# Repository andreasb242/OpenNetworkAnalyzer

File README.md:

# OpenNetworkAnalyzer
Improved software for https://hackaday.io/project/10021-arduino-network-analyzer

## Hardware
There are different hardware implementations, some based on Arduino, for an easy Start.

### Arduino
*firmware/arduino/ONA_PWM* is a firmware, which does not need any additional hardware.
The Pin *D5* is used as output, without any filtering, the Pin *A0* is used as input.
This firmware can be used to easy check how it's working, wihtout bying / building hardware.

But the output is a rectangular signal, which isn't really working for testing, as a rectangular signal contains different frequenecies instead of one.
Therefore this is only for testing purpose.

*Maximum Frequency* is 62500Hz, really low.

*firmware/arduino/ONA_AD9851* is the Version based on the first software-hackday.io Version.
There is the Arduino Uno Shield, layout located at *layout/hackaday.io-V2.0*.

And there is an Arduino Nano Version, located at *layout/arduino-nano-AD9851*
This board is not tested.

*firmware/arduino/ONA_SI5351*
This implementation is fully working from 4kHz to 175MHz, recommend range is about 1MHz to 100MHz, out of this range there are some issues: at 4kHz the Sinus looks more than a Square wave.
At > 100MHz the signal gets lower.

### STM32 USB
Not yet ready.

## Screenshots

## Installation / running
### Ubuntu
    git clone https://github.com/andreasb242/OpenNetworkAnalyzer.git
    sudo apt install python3-tk python3-numpy python3-serial python3-pil.imagetk
    cd software
    python3 main.py

### Mac OS
    TODO

### Windows
    TODO

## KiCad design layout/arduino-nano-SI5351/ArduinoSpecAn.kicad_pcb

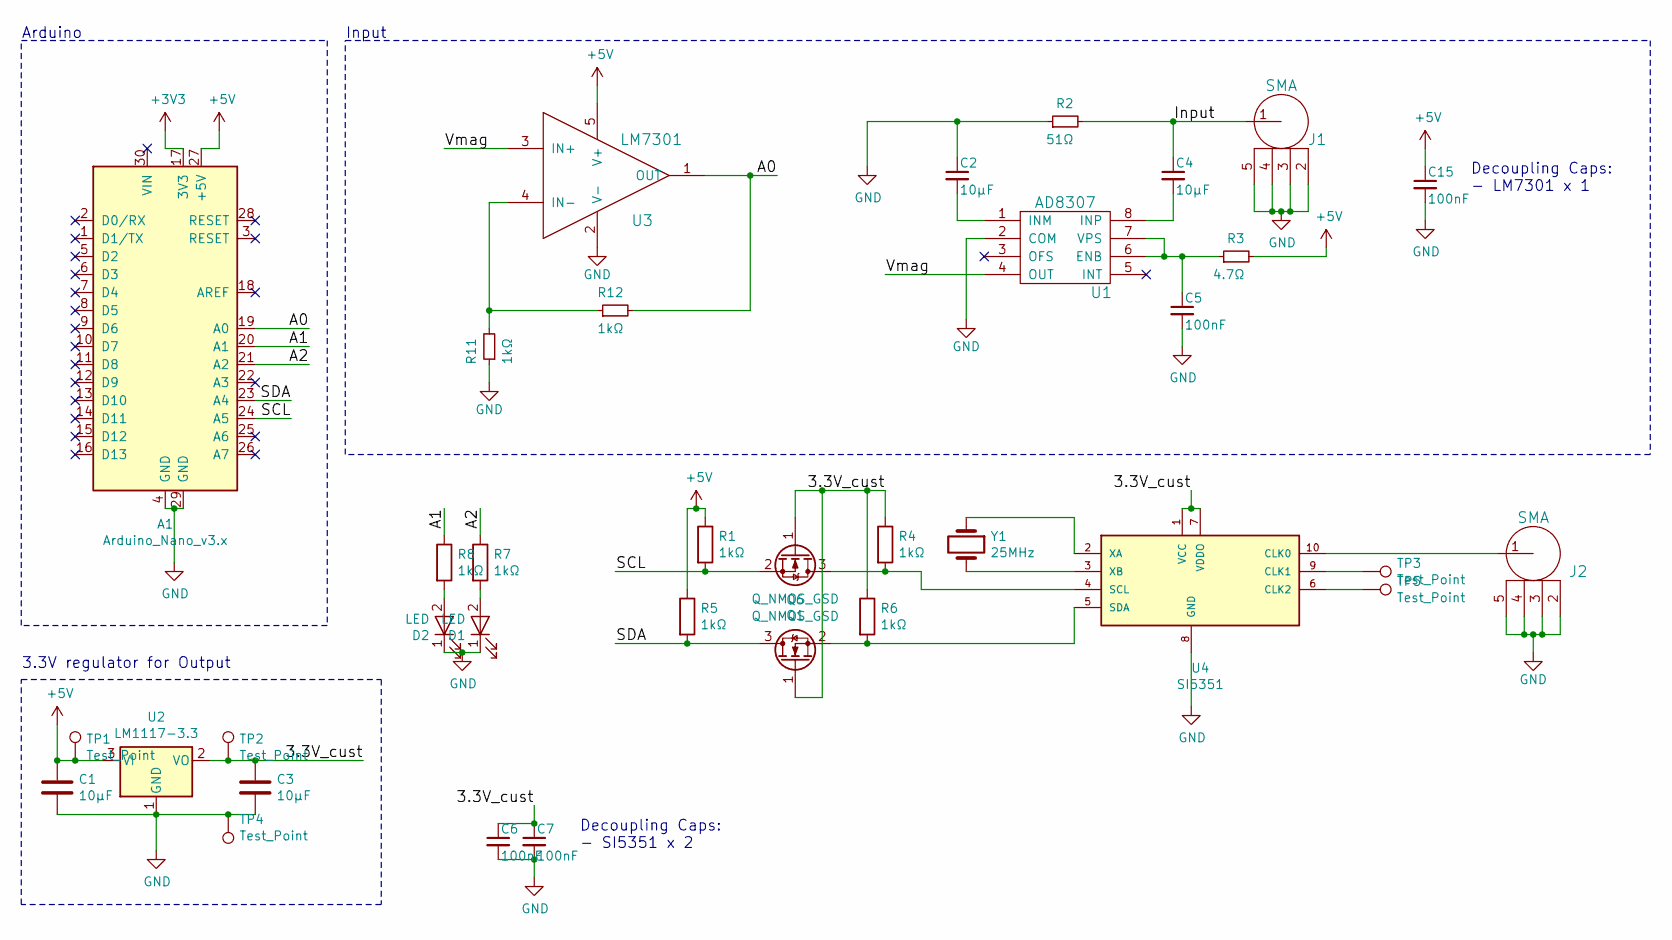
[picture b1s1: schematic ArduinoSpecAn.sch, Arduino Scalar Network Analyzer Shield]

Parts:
A1: Arduino_Nano_v3.x; Arduino_Nano
C1, C2, C3, C4: 10µF; C_0805_2012Metric_Pad1.15x1.50mm_HandSolder
C5, C6, C7, C15: 100nF; C_0805_2012Metric_Pad1.15x1.50mm_HandSolder
D1, D2: LED; LED_0805_2012Metric_Pad0.97x1.50mm_HandSolder
J1, J2: SMA; SMA_Edgemount
Q1, Q6: Q_NMOS_GSD; SOT-23
R1, R4, R5, R6, R7, R8, R11, R12: 1kΩ; R_0805_2012Metric_Pad1.15x1.50mm_HandSolder
R2: 51Ω; R_0805_2012Metric_Pad1.15x1.50mm_HandSolder
R3: 4.7Ω; R_0805_2012Metric_Pad1.15x1.50mm_HandSolder
TP1, TP2, TP3, TP4, TP5: Test_Point; TestPoint_Pad_D1.5mm
U1: AD8307; SOIC-8-N
U2: LM1117-3.3; SOT-223-3_TabPin2
U3: LM7301; SOT-23-5
U4: SI5351; MSOP-10_3x3mm_P0.5mm
Y1: 25MHz; Crystal_HC49-U_Vertical

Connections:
+5V: A1.27 (+5V), C1.1, C15.1, R1.1, R3.2, R5.1, TP1.1, U2.3 (VI), U3.5 (V+)
/3.3V_cust: C3.1, C6.1, C7.1, Q1.1 (G), Q6.1 (G), R4.1, R6.1, TP2.1, U2.2 (VO), U4.1 (VCC), U4.7 (VDDO)
/A0: A1.19 (A0), R12.2, U3.1 (OUT)
/A1: A1.20 (A1), R8.1
/A2: A1.21 (A2), R7.1
/Input: C4.1, J1.1, R2.2
/SCL: A1.24 (A5), Q1.2 (S), R1.2
/SDA: A1.23 (A4), Q6.3 (D), R5.2
/Vmag: U1.4 (OUT), U3.3 (IN+)
GND: A1.4 (GND), A1.29 (GND), C1.2, C2.1, C3.2, C5.2, C6.2, C7.2, C15.2, D1.1 (K), D2.1 (K), J1.2, J1.3, J1.4, J1.5, J2.2, J2.3, J2.4, J2.5, R2.1, R11.1, TP4.1, U1.2 (COM), U2.1 (GND), U3.2 (V-), U4.8 (GND)
unnamed: C2.2, U1.1 (INM)
unnamed: C4.2, U1.8 (INP)
unnamed: C5.1, R3.1, U1.6 (ENB), U1.7 (VPS)
unnamed: D1.2 (A), R7.2
unnamed: D2.2 (A), R8.2
unnamed: J2.1, U4.10 (CLK0)
unnamed: Q1.3 (D), R4.2, U4.4 (SCL)
unnamed: Q6.2 (S), R6.2, U4.5 (SDA)
unnamed: R11.2, R12.1, U3.4 (IN-)
unnamed: TP3.1, U4.9 (CLK1)
unnamed: TP5.1, U4.6 (CLK2)
unnamed: U4.2 (XA), Y1.1
unnamed: U4.3 (XB), Y1.2

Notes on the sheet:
Decoupling Caps: - LM7301 x 1
Arduino
Input
Decoupling Caps: - SI5351 x 2
3.3V regulator for Output

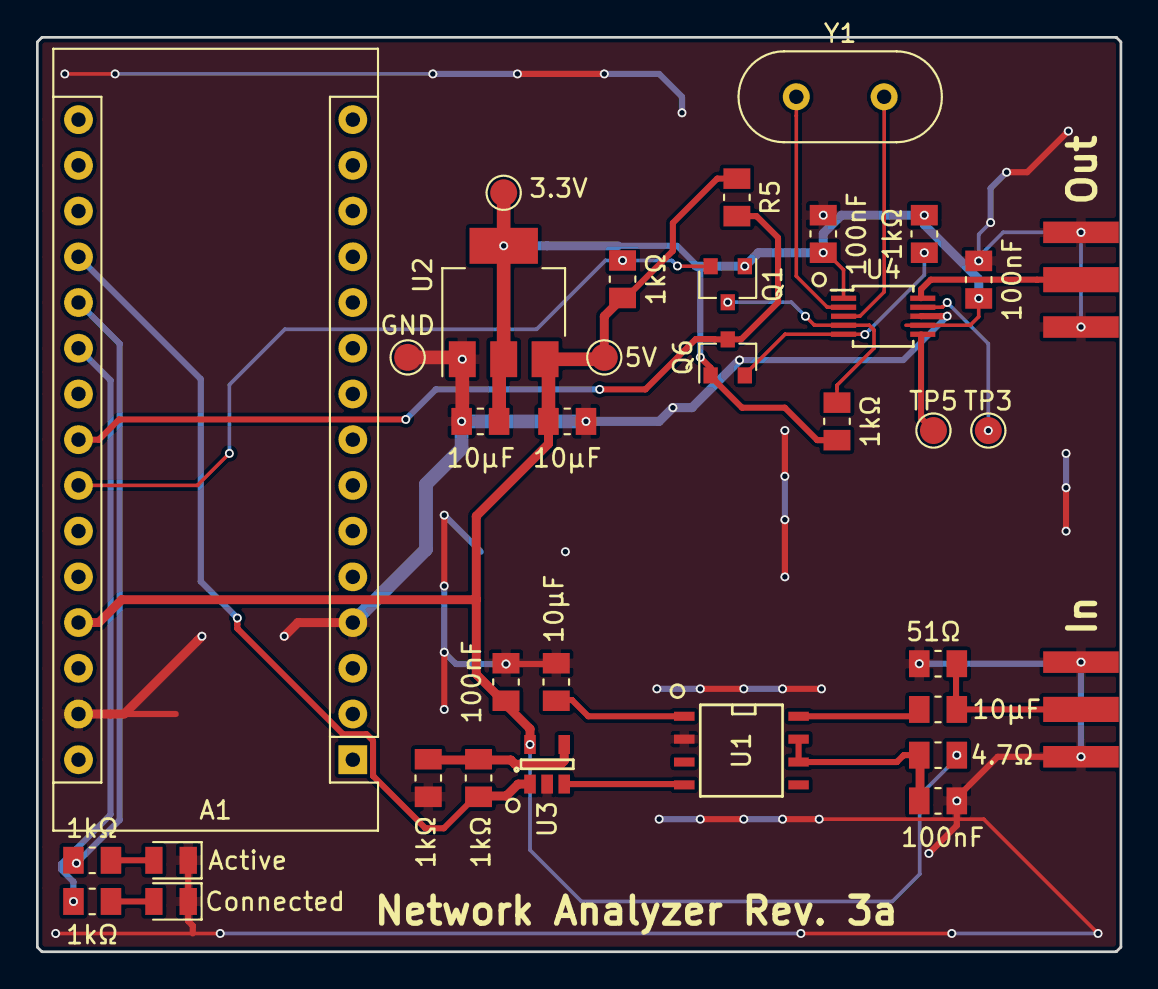
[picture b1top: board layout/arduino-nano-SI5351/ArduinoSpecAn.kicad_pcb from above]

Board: 2 copper layers, 60.2 x 50.8 mm, 35 parts (0 on the bottom side), 23 nets.

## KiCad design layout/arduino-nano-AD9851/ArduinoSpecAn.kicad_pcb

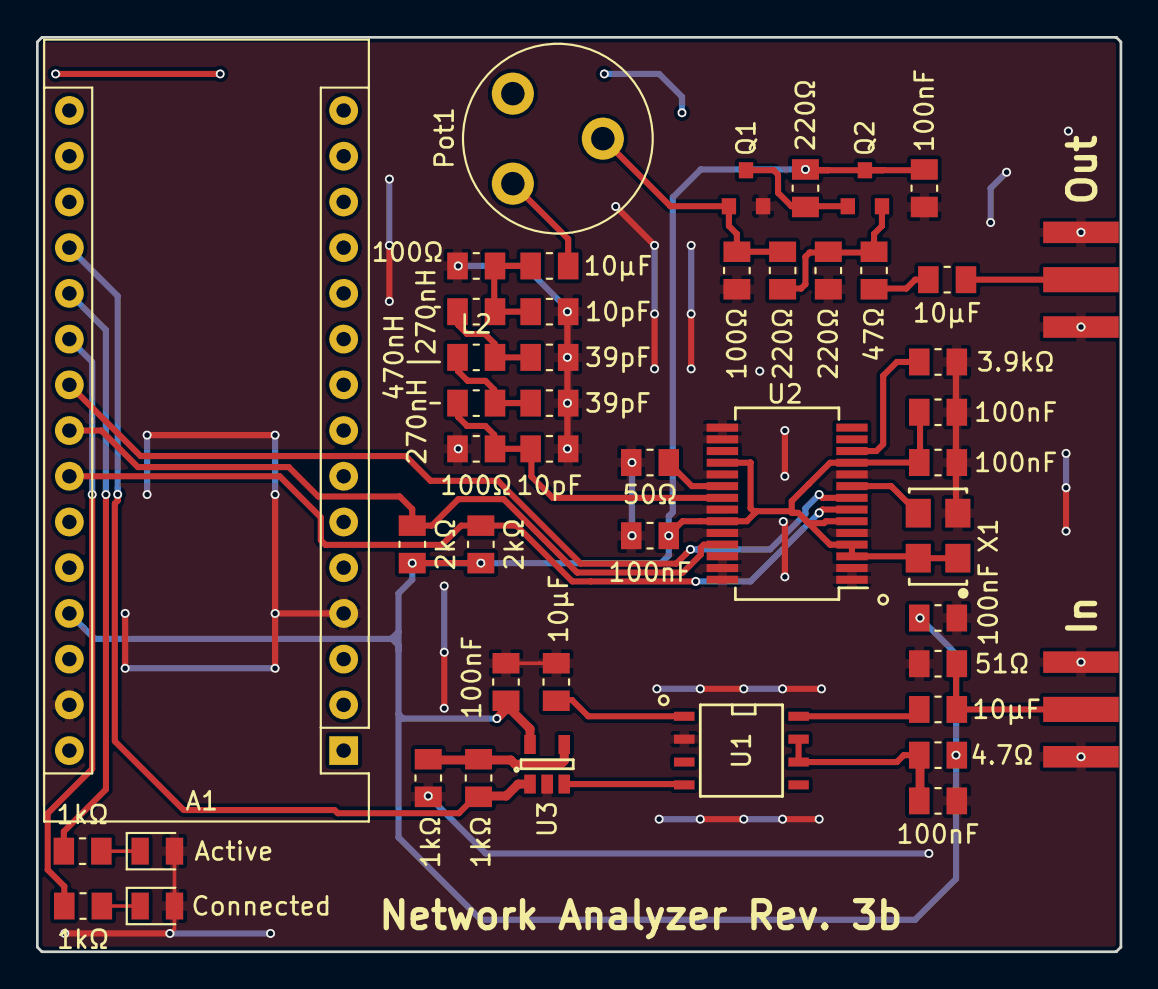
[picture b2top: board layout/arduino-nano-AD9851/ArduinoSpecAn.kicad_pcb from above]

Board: 2 copper layers, 60.2 x 50.8 mm, 47 parts (0 on the bottom side), 29 nets.

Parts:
A1: Arduino_Nano_v3.x; Arduino_Nano
C1, C5, C11, C12, C13, C14, C15: 100nF; C_0805_2012Metric_Pad1.15x1.50mm_HandSolder
C2, C3, C4, C6: 10µF; C_0805_2012Metric_Pad1.15x1.50mm_HandSolder
C7, C10: 10pF; C_0805_2012Metric_Pad1.15x1.50mm_HandSolder
C8, C9: 39pF; C_0805_2012Metric_Pad1.15x1.50mm_HandSolder
D1, D2: LED; LED_0805_2012Metric_Pad0.97x1.50mm_HandSolder
J1, J2: SMA; SMA_Edgemount
L1, L3: 270nH; L_0805_2012Metric_Pad1.15x1.50mm_HandSolder
L2: 470nH; L_0805_2012Metric_Pad1.15x1.50mm_HandSolder
Pot1: 1k; Potentiometer_Piher_PT-10-V05_Vertical
Q1, Q2: MMBT3904; SOT-23
R1: 3.9kΩ; R_0805_2012Metric_Pad1.15x1.50mm_HandSolder
R2: 51Ω; R_0805_2012Metric_Pad1.15x1.50mm_HandSolder
R3: 4.7Ω; R_0805_2012Metric_Pad1.15x1.50mm_HandSolder
R4, R10, R13: 100Ω; R_0805_2012Metric_Pad1.15x1.50mm_HandSolder
R5, R6, R7: 220Ω; R_0805_2012Metric_Pad1.15x1.50mm_HandSolder
R8: 47Ω; R_0805_2012Metric_Pad1.15x1.50mm_HandSolder
R9: 50Ω; R_0805_2012Metric_Pad1.15x1.50mm_HandSolder
R11, R12, R16, R17: 1kΩ; R_0805_2012Metric_Pad1.15x1.50mm_HandSolder
R14, R15: 2kΩ; R_0805_2012Metric_Pad1.15x1.50mm_HandSolder
U1: AD8307; SOIC-8-N
U2: AD9851; SSOP-28_5.3x10.2mm_Pitch0.65mm
U3: LM7301; SOT-23-5
X1: KC5032A; KC5032A-CM_SMD_Crystal

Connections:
/5V: A1.27, C1.1, C11.1, C12.1, C13.1, C14.1, C15.1, Q2.3, R3.2, R5.1, R14.1, R15.1, U2.3, U2.4, U2.6, U2.11, U2.18, U2.23, U3.5, X1.1, X1.4
/A0: A1.19, R12.2, U3.1
/A1: A1.20, R16.1
/A2: A1.21, R17.1
/Input: C4.1, J1.1, R2.2
/RF: C3.1, C10.1, L3.2, R13.1
/SCL: A1.24, R14.2, U2.7
/SDA: A1.23, R15.2, U2.25
/SLD: A1.22, U2.8
/Vmag: U1.4, U3.3
GND: A1.4, A1.29, C1.2, C2.1, C5.2, C7.2, C8.2, C9.2, C10.2, C11.2, C12.2, C13.2, C14.2, C15.2, D1.2, D2.2, J1.2, J1.3, J1.4, J1.5, J2.2, J2.3, J2.4, J2.5, Q1.2, R1.2, R2.1, R4.2, R7.2, R9.2, R10.2, R11.1, R13.2, U1.2, U2.1, U2.2, U2.5, U2.10, U2.15, U2.16, U2.19, U2.22, U2.24, U2.26, U2.27, U2.28, U3.2, X1.2
unnamed: C2.2, U1.1
unnamed: C3.2, Pot1.1
unnamed: C4.2, U1.8
unnamed: C5.1, R3.1, U1.6, U1.7
unnamed: C6.1, R8.2
unnamed: C6.2, J2.1
unnamed: C7.1, L1.1, R10.1, U2.21
unnamed: C8.1, L1.2, L2.1
unnamed: C9.1, L2.2, L3.1
unnamed: D1.1, R16.2
unnamed: D2.1, R17.2
unnamed: Pot1.2, Q1.1, R4.1, R6.1
unnamed: Q1.3, Q2.1, R5.2
unnamed: Q2.2, R6.2, R7.1, R8.1
unnamed: R1.1, U2.12
unnamed: R9.1, U2.20
unnamed: R11.2, R12.1, U3.4
unnamed: U2.9, X1.3

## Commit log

2018-08-01 Layout files
    Working on Arduino nano layout
2018-08-01 Working on layout
2018-08-01 Removed DDS
2018-08-01 Layout
2018-08-01 Mostly finished
2018-08-01 Added reworked app
2018-08-01 Dummy read working
2018-08-01 Gui Toolbar
2018-08-01 Added icons for toolbar
2018-08-01 Removed buttons
2018-08-01 Toolbar, allow to configure frequency range
2018-08-01 Working on Hardware classes
2018-08-02 Arduino PWM Firmware working
2018-08-02 Window Handling
2018-08-02 Arduino with PMW Firmware is working
2018-08-02 Arduino PWM Display working
2018-08-02 Calibration working, About Dialog
2018-08-02 Auto center option
2018-08-02 Hardware detection, todos added
2018-08-03 Added soldermask (Gerber) Center view now working even if referenced
2018-08-03 Layout is resized
2018-08-03 Calibration can be cleared
2018-08-03 Footer Implemented
2018-08-03 Graph Size
2018-08-03 Footer, connection state
2018-08-03 Display errors
2018-08-03 Arduino Firmware
2018-08-03 Hardware access loading separated into another class
2018-08-03 Listener for hardware events
2018-08-03 Hardware switch working
2018-08-03 Apply hardware settings
2018-08-03 Load Port Settings
2018-08-03 Validation, GUI
2018-08-03 Ui fully working
2018-08-03 Added Screenshot
2018-08-03 Speedtest
2018-08-03 Readme
2018-08-23 SI5351 Output working
2018-08-24 Connection lost handling
2018-08-24 Display errors with red background, fixed UI Bugs
2018-08-24 Launcher and some Improvements
2018-08-24 Launcher
2018-08-24 Display values in Header
2018-08-24 Show db/div in Header
2018-08-24 Moved reference to header
2018-08-24 Removed graph footer texts
2018-08-24 Units Fixed
2018-08-25 Icon and launcher fully working
2018-08-25 Show / Hide current position marker
2018-08-25 Allow to switch style
2018-08-26 Board Version handling
2018-08-26 Faster connect
2018-08-26 Store Settings
2018-08-26 Load / Store settings
2018-08-26 Screenshot updated
2018-08-26 Play / Pause, fixed bugs
2018-08-26 Added image, fixed bug
2018-08-26 fixed bugs, updated screenshot
2018-08-26 Updated Screenshot
2018-08-29 Fixed play / pause image
